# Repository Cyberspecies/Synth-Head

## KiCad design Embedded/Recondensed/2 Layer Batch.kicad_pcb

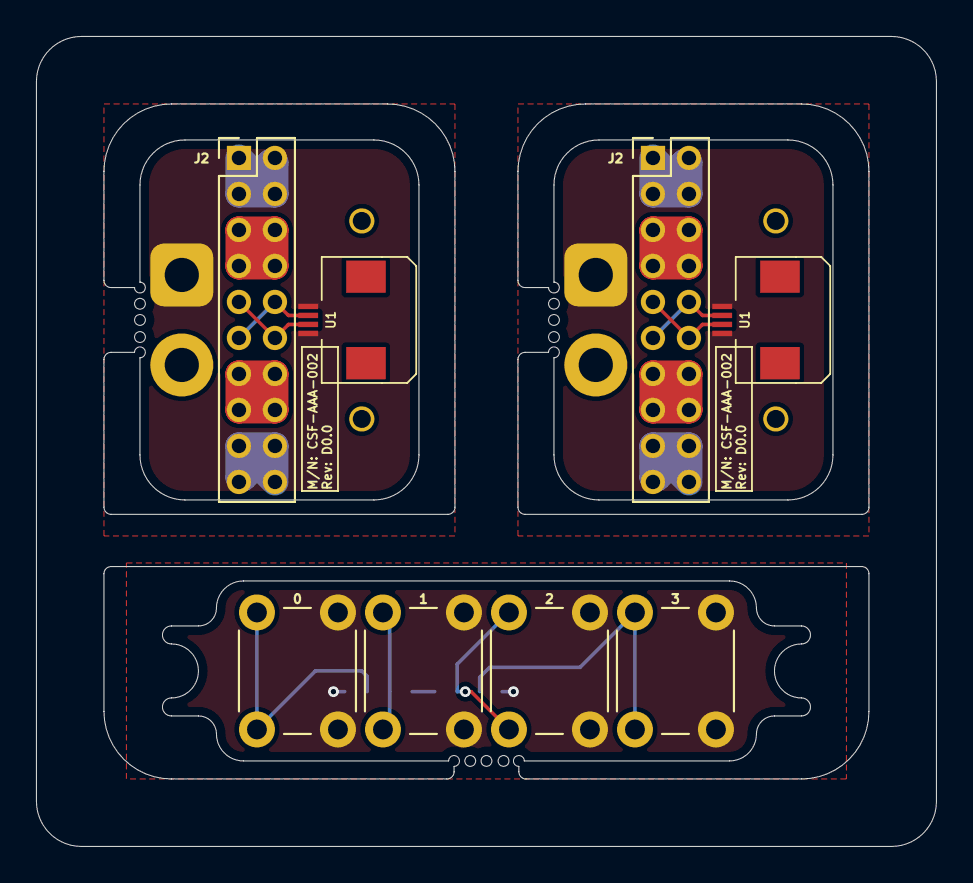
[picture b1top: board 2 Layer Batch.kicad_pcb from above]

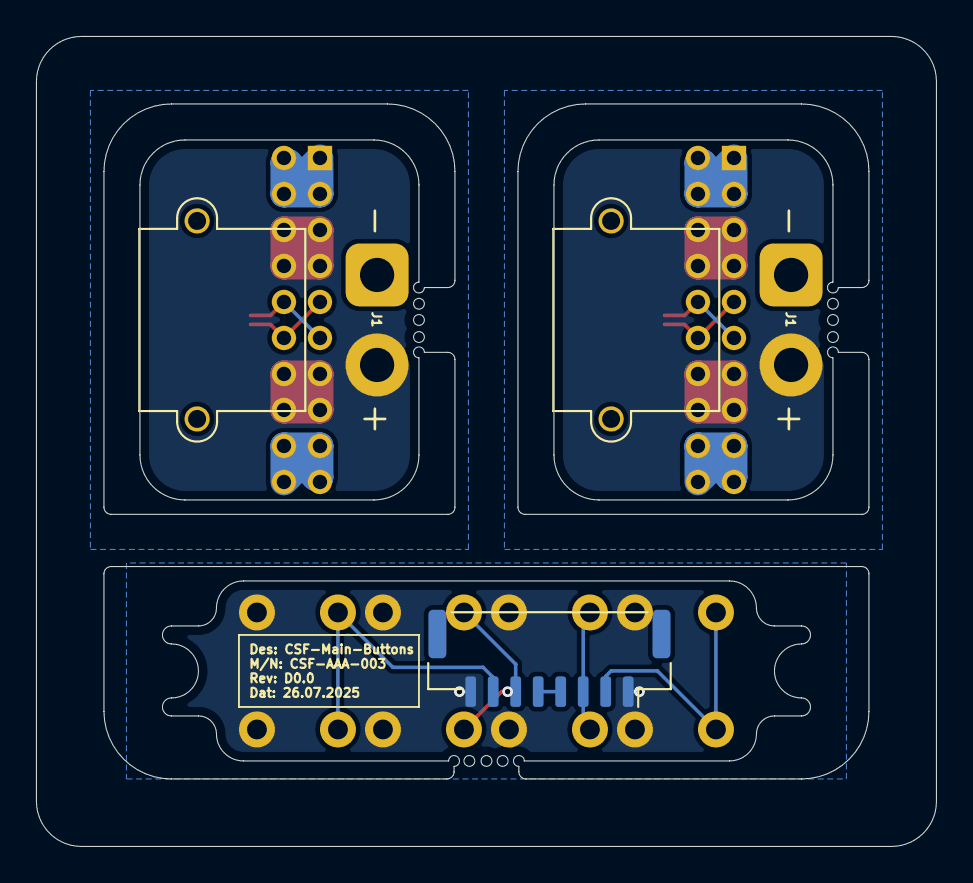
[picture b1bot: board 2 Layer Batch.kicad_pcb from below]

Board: 2 copper layers, 50.0 x 45.0 mm, 11 parts (3 on the bottom side), 9 nets.

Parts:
J1, J1#2: Substructure Power; AMASS_XT30PW-M_1x02_P2.50mm_Horizontal
J2, J2#2: Pogo Pins; PinHeader_2x10_P2.00mm_Vertical
J8: Buttons; JST_GH_SM08B-GHS-TB_1x08-1MP_P1.25mm_Horizontal
SW1: 0; SW_PUSH_6mm_H5mm
SW2: 1; SW_PUSH_6mm_H5mm
SW3: 2; SW_PUSH_6mm_H5mm
SW4: 3; SW_PUSH_6mm_H5mm
U1, U1#2: Substructure; FFC-4-0.5

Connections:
+3V3: J8.4, J8.5
+RAWVS: J1.2, J1#2.2, J2.5, J2.6, J2.7, J2.8, J2.13, J2.14, J2.15, J2.16, J2#2.5, J2#2.6, J2#2.7, J2#2.8, J2#2.13, J2#2.14, J2#2.15, J2#2.16
Button 0: J8.2, SW1.1
Button 1: J8.3, SW2.1
Button 2: J8.6, SW3.1
Button 3: J8.7, SW4.1
GND: J1.1, J1#2.1, J2.1, J2.2, J2.3, J2.4, J2.17, J2.18, J2.19, J2.20, J2#2.1, J2#2.2, J2#2.3, J2#2.4, J2#2.17, J2#2.18, J2#2.19, J2#2.20, J8.1, J8.8, SW1.2, SW2.2, SW3.2, SW4.2, U1.1, U1.4, U1#2.1, U1#2.4
Power UART RX: J2.9, J2.12, J2#2.9, J2#2.12, U1.2, U1#2.2
Power UART TX: J2.10, J2.11, J2#2.10, J2#2.11, U1.3, U1#2.3

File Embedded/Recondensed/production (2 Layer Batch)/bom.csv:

Designator,Footprint,Quantity,Value,LCSC Part #
"J1_2, J1",AMASS_XT30PW-M_1x02_P2.50mm_Horizontal,2,Substructure Power,
"J2_2, J2",PinHeader_2x10_P2.00mm_Vertical,2,Pogo Pins,
J8,JST_GH_SM08B-GHS-TB_1x08-1MP_P1.25mm_Horizontal,1,Buttons,
SW1,SW_PUSH_6mm_H5mm,1,0,
SW2,SW_PUSH_6mm_H5mm,1,1,
SW3,SW_PUSH_6mm_H5mm,1,2,
SW4,SW_PUSH_6mm_H5mm,1,3,
"U1_2, U1",FFC-4-0.5,2,Substructure,

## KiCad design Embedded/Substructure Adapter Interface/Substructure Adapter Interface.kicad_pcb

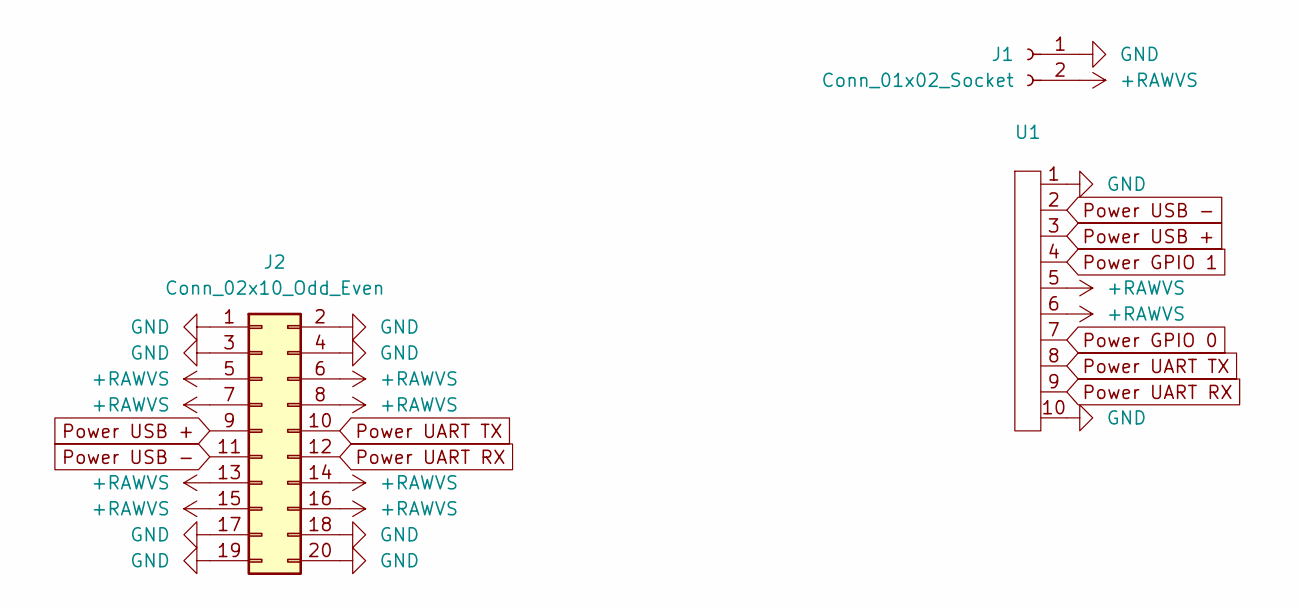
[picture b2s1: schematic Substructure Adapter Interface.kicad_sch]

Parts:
J1: Conn_01x02_Socket; AMASS_XT30PW-M_1x02_P2.50mm_Horizontal
J2: Conn_02x10_Odd_Even; PinHeader_2x10_P1.00mm_Vertical
U1: FFC 0.8mm 10P

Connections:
+RAWVS: J1.2, J2.5, J2.6, J2.7, J2.8, J2.13, J2.14, J2.15, J2.16, U1.5, U1.6
GND: J1.1, J2.1, J2.2, J2.3, J2.4, J2.17, J2.18, J2.19, J2.20, U1.1, U1.10
Power GPIO 0: U1.7
Power GPIO 1: U1.4
Power UART RX: J2.12, U1.9
Power UART TX: J2.10, U1.8
Power USB +: J2.9, U1.3
Power USB -: J2.11, U1.2

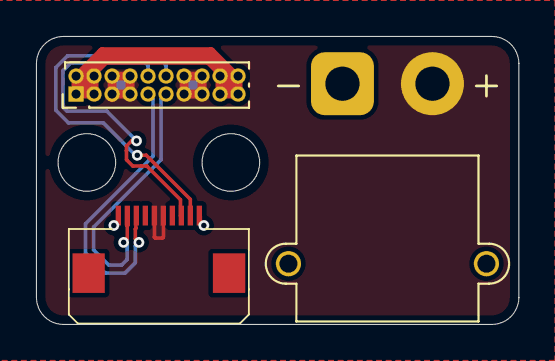
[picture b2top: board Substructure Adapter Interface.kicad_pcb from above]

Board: 2 copper layers, 26.8 x 16.0 mm, 3 parts (0 on the bottom side), 6 nets.

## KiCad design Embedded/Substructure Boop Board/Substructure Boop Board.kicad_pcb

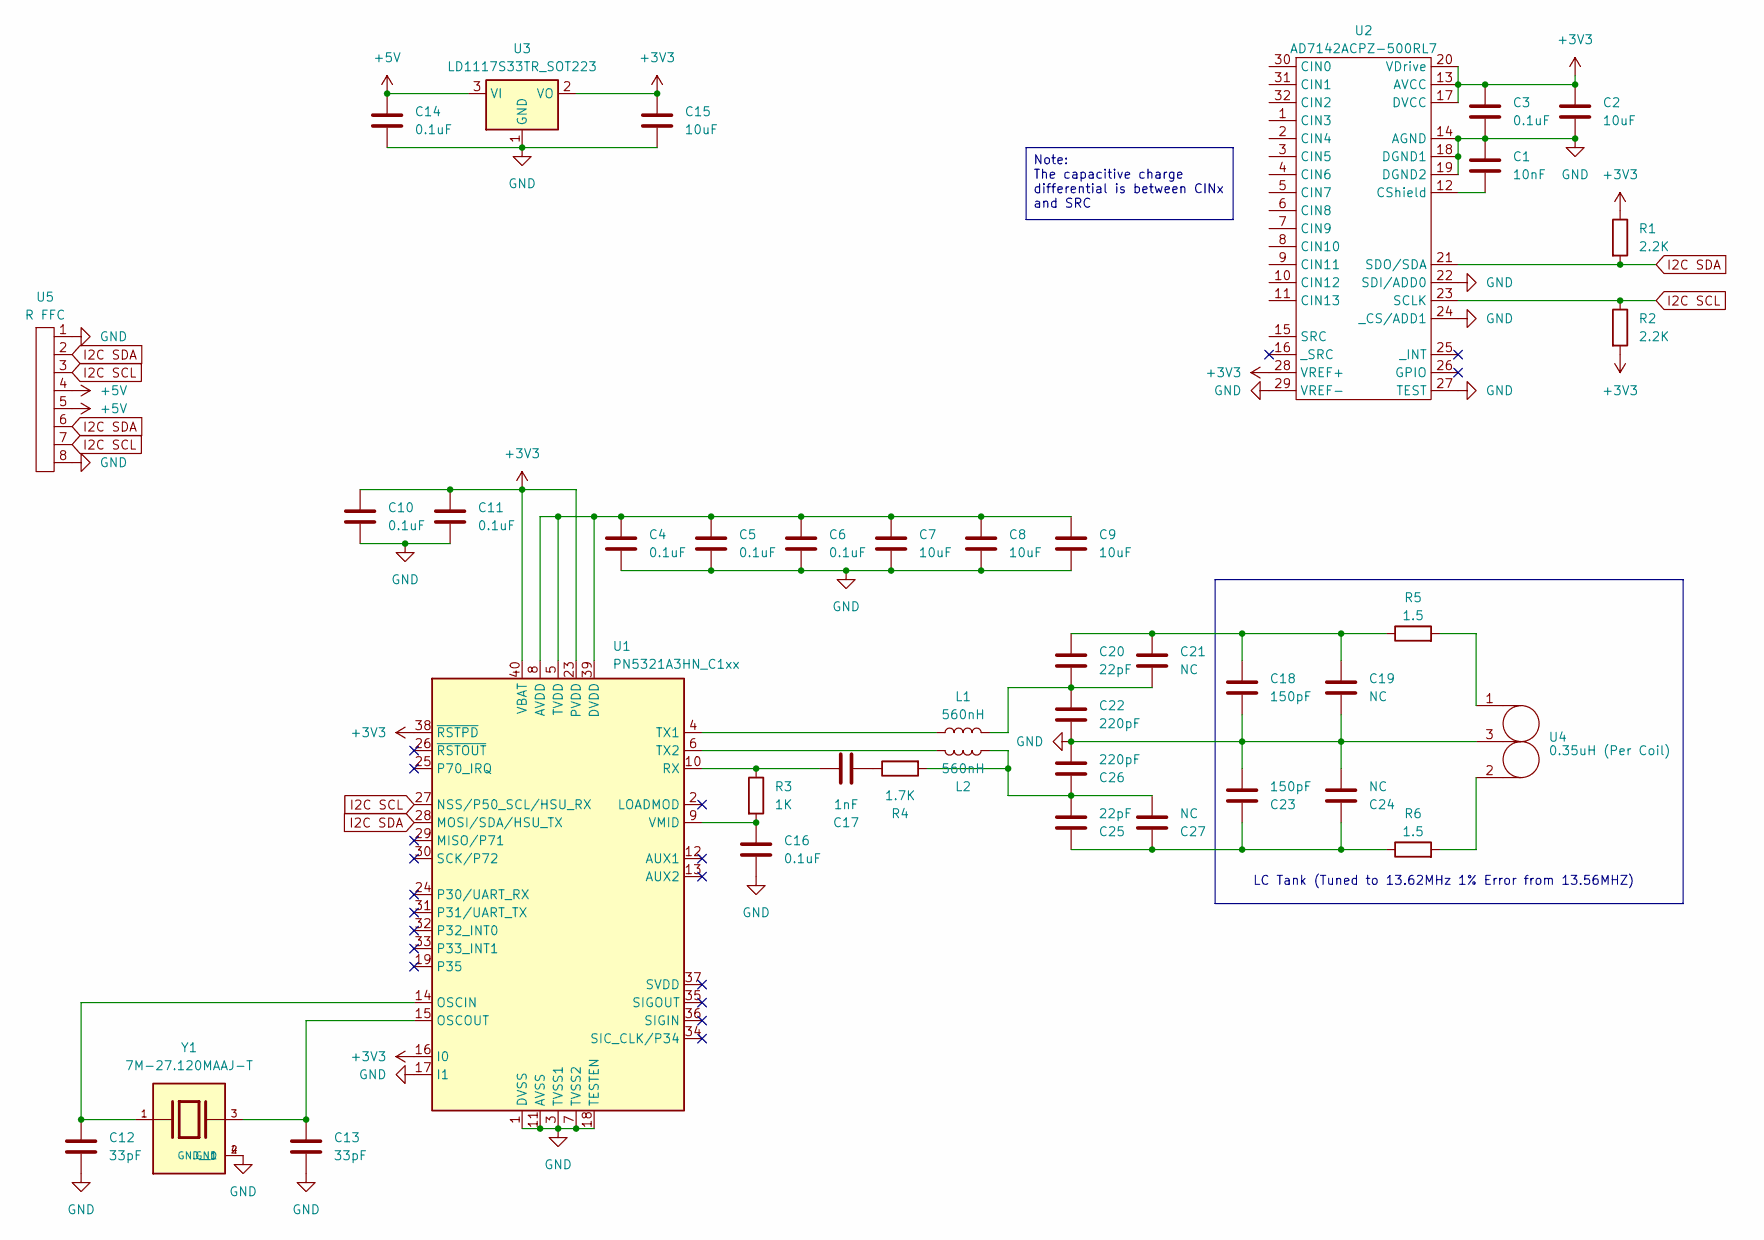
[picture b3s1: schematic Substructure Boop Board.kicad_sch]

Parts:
C1: 10nF; C_0402_1005Metric_Pad0.74x0.62mm_HandSolder
C2, C7, C8, C9: 10uF; C_0402_1005Metric_Pad0.74x0.62mm_HandSolder
C3, C4, C5, C6, C10, C11, C16: 0.1uF; C_0402_1005Metric_Pad0.74x0.62mm_HandSolder
C12, C13: 33pF; C_0402_1005Metric_Pad0.74x0.62mm_HandSolder
C14: 0.1uF; C_0603_1608Metric_Pad1.08x0.95mm_HandSolder
C15: 10uF; C_0603_1608Metric_Pad1.08x0.95mm_HandSolder
C17: 1nF; C_0402_1005Metric_Pad0.74x0.62mm_HandSolder
C18, C23: 150pF; C_0402_1005Metric_Pad0.74x0.62mm_HandSolder
C19, C21, C24, C27: NC; C_0402_1005Metric_Pad0.74x0.62mm_HandSolder
C20, C25: 22pF; C_0402_1005Metric_Pad0.74x0.62mm_HandSolder
C22, C26: 220pF; C_0402_1005Metric_Pad0.74x0.62mm_HandSolder
L1, L2: 560nH; L_0603_1608Metric_Pad1.05x0.95mm_HandSolder
R1, R2: 2.2K; C_0402_1005Metric_Pad0.74x0.62mm_HandSolder
R3: 1K; C_0402_1005Metric_Pad0.74x0.62mm_HandSolder
R4: 1.7K; C_0402_1005Metric_Pad0.74x0.62mm_HandSolder
R5, R6: 1.5; C_0402_1005Metric_Pad0.74x0.62mm_HandSolder
U1: PN5321A3HN_C1xx; HVQFN-40-1EP_6x6mm_P0.5mm_EP4.1x4.1mm; LCSC C28925
U2: AD7142ACPZ-500RL7; LFCSP-32-1EP_5x5mm_P0.5mm_EP3.1x3.1mm_ThermalVias; LCSC C208139
U3: LD1117S33TR_SOT223; SOT-223-3_TabPin2; LCSC C86781
U4: 0.35uH (Per Coil); 30 x 40 - 2 Pair 2 Layer 2 Turn Loop Antenna
U5: R FFC; FFC 0.8mm 8P
Y1: 7M-27.120MAAJ-T; XTAL_7M-27.120MAAJ-T; PARTREV N/A; DIGIKEY 887-1424-1-ND

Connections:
+3V3: C2.1, C3.1, C10.1, C11.1, C15.1, R1.1, R2.2, U1.16 (I0), U1.23 (PVDD), U1.38 (~RSTPD), U1.40 (VBAT), U2.13 (AVCC), U2.17 (DVCC), U2.20 (VDrive), U2.28 (VREF+), U3.2 (VO)
+5V: C14.1, U3.3 (VI), U5.4, U5.5
GND: C1.1, C2.2, C3.2, C4.2, C5.2, C6.2, C7.2, C8.2, C9.2, C10.2, C11.2, C12.2, C13.2, C14.2, C15.2, C16.2, C18.2, C19.2, C22.2, C23.2, C24.2, C26.1, U1.1 (DVSS), U1.3 (TVSS1), U1.7 (TVSS2), U1.11 (AVSS), U1.17 (I1), U1.18 (TESTEN), U1.41 (AVSS), U2.14 (AGND), U2.18 (DGND1), U2.19 (DGND2), U2.22 (SDI/ADD0), U2.24 (_CS/ADD1), U2.27 (TEST), U2.29 (VREF-), U3.1 (GND), U4.3, U5.1, U5.8, Y1.2 (GND), Y1.4 (GND__1)
I2C SCL: R2.1, U1.27 (NSS/P50_SCL/HSU_RX), U2.23 (SCLK), U5.3, U5.7
I2C SDA: R1.2, U1.28 (MOSI/SDA/HSU_TX), U2.21 (SDO/SDA), U5.2, U5.6
unnamed: C17.2, R4.1
unnamed: C18.1, C19.1, C20.1, C21.1, R5.1
unnamed: C20.2, C21.2, C22.1, L1.2
unnamed: C23.1, C24.1, C25.1, C27.1, R6.1
unnamed: C25.2, C26.2, C27.2, L2.2, R4.2
unnamed: R5.2, U4.1
unnamed: R6.2, U4.2
unnamed: C4.1, C5.1, C6.1, C7.1, C8.1, C9.1, U1.5 (TVDD), U1.8 (AVDD), U1.39 (DVDD)
unnamed: C12.1, U1.14 (OSCIN), Y1.1
unnamed: C13.1, U1.15 (OSCOUT), Y1.3
unnamed: C17.1, R3.1, U1.10 (RX)
unnamed: L1.1, U1.4 (TX1)
unnamed: L2.1, U1.6 (TX2)
unnamed: C16.1, R3.2, U1.9 (VMID)
unnamed: C1.2, U2.12 (CShield)

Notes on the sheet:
LC Tank (Tuned to 13.62MHz 1% Error from 13.56MHZ)
Note: The capacitive charge differential is between CINx and SRC

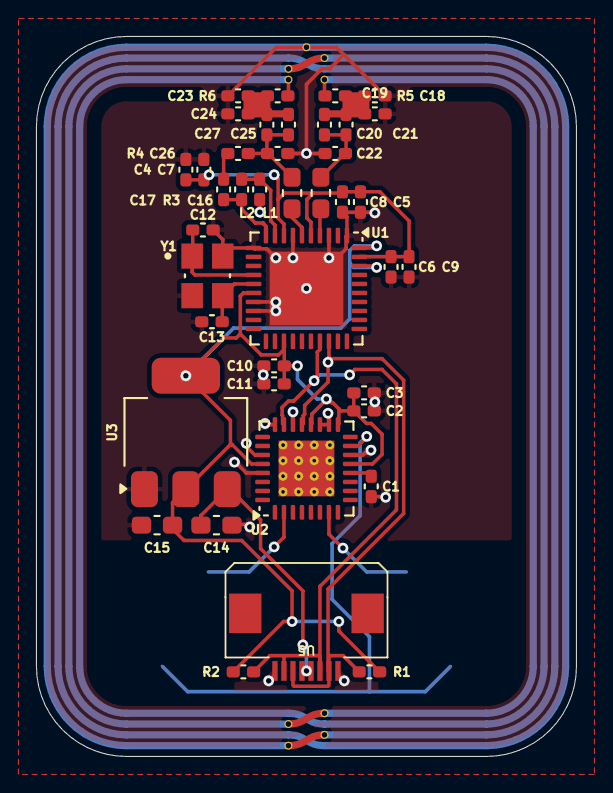
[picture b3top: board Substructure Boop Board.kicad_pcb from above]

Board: 2 copper layers, 30.0 x 40.0 mm, 41 parts (1 on the bottom side), 20 nets.

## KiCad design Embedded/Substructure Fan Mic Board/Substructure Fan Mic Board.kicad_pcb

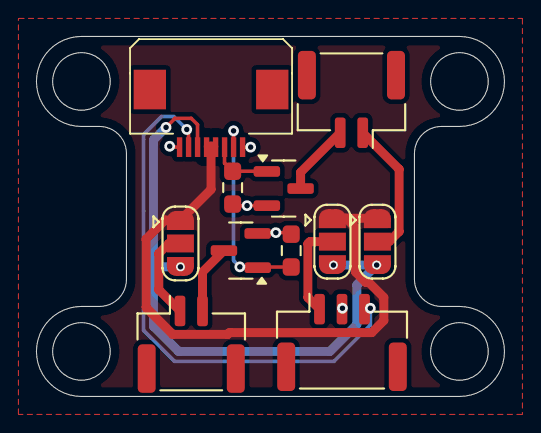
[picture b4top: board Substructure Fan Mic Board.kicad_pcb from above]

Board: 2 copper layers, 26.0 x 20.0 mm, 11 parts (0 on the bottom side), 11 nets.

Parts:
J1: Conn_01x03_Socket; JST_GH_SM03B-GHS-TB_1x03-1MP_P1.25mm_Horizontal
J2, J3: Conn_01x02_Socket; JST_GH_SM02B-GHS-TB_1x02-1MP_P1.25mm_Horizontal
JP1, JP2, JP3: SolderJumper_3_Open; SolderJumper-3_P1.3mm_Open_RoundedPad1.0x1.5mm
Q1, Q2: DMG3402L; SOT-23
R1, R2: 10K; R_0603_1608Metric_Pad0.98x0.95mm_HandSolder
U2: F FFC; FFC 0.8mm 8P

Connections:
+3V3: JP1.3 (B), JP2.3 (B), JP3.3 (B), U2.6
+5V: JP1.1 (A), JP2.1 (A), JP3.1 (A), U2.4, U2.5
Fan 0: Q1.1 (G), R1.1, U2.3
Fan 1: Q2.1 (G), R2.1, U2.2
GND: J1.2, Q1.2 (S), Q2.2 (S), R1.2, R2.2, U2.1, U2.8
Mic Analog: J1.3, U2.7
unnamed: J1.1, JP1.2 (C)
unnamed: J2.1, JP2.2 (C)
unnamed: J2.2, Q1.3 (D)
unnamed: J3.1, JP3.2 (C)
unnamed: J3.2, Q2.3 (D)

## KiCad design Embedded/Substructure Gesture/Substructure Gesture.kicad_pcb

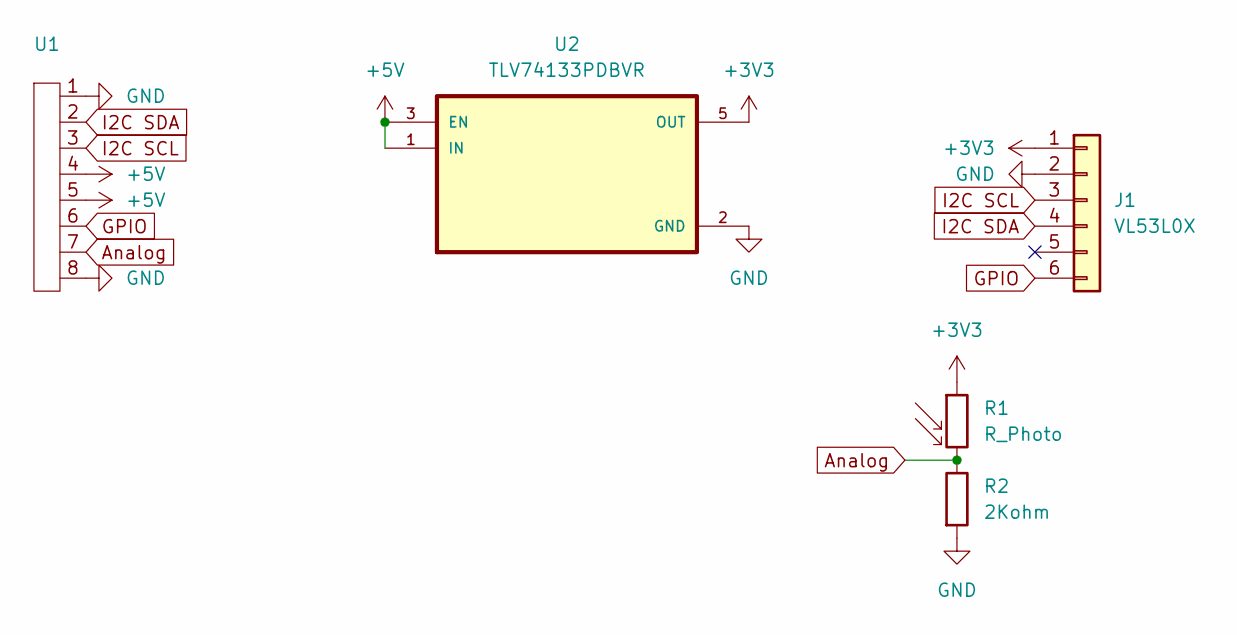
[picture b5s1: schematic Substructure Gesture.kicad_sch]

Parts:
J1: VL53L0X; PinHeader_1x06_P2.54mm_Vertical
R1: R_Photo; R_LDR_5.1x4.3mm_P3.4mm_Vertical
R2: 2Kohm; R_0603_1608Metric_Pad0.98x0.95mm_HandSolder
U1: FFC 0.8mm 8P
U2: TLV74133PDBVR; SOT95P280X145-5N

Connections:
+3V3: J1.1, R1.1, U2.5 (OUT)
+5V: U1.4, U1.5, U2.1 (IN), U2.3 (EN)
Analog: R1.2, R2.1, U1.7
GND: J1.2, R2.2, U1.1, U1.8, U2.2 (GND)
GPIO: J1.6, U1.6
I2C SCL: J1.3, U1.3
I2C SDA: J1.4, U1.2

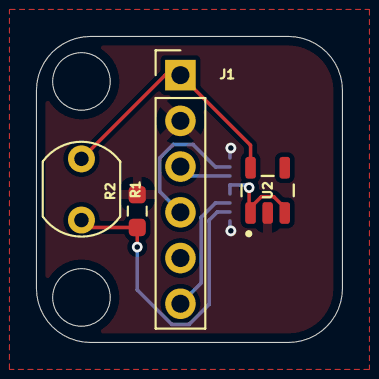
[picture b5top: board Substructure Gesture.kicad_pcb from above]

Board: 2 copper layers, 17.0 x 17.0 mm, 5 parts (1 on the bottom side), 7 nets.

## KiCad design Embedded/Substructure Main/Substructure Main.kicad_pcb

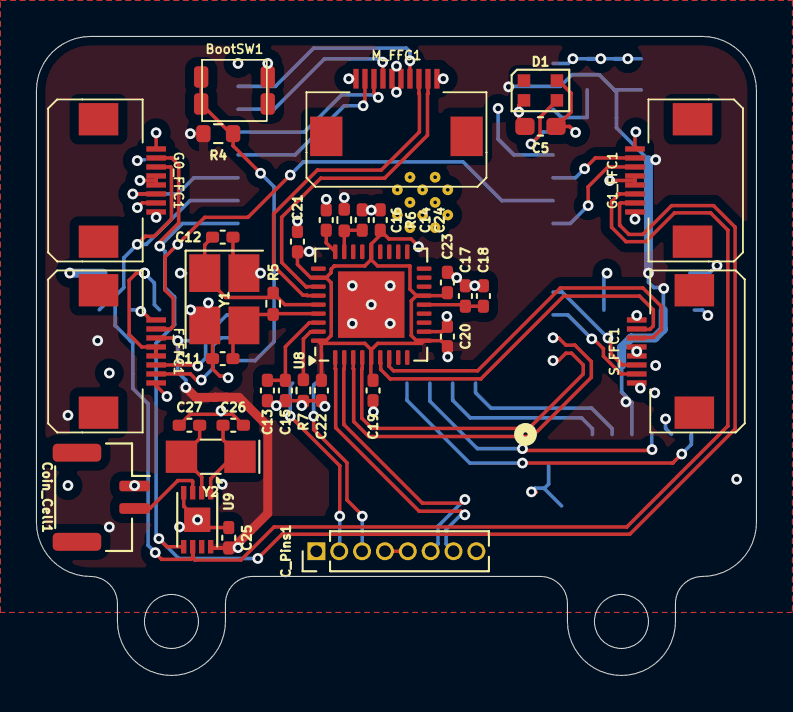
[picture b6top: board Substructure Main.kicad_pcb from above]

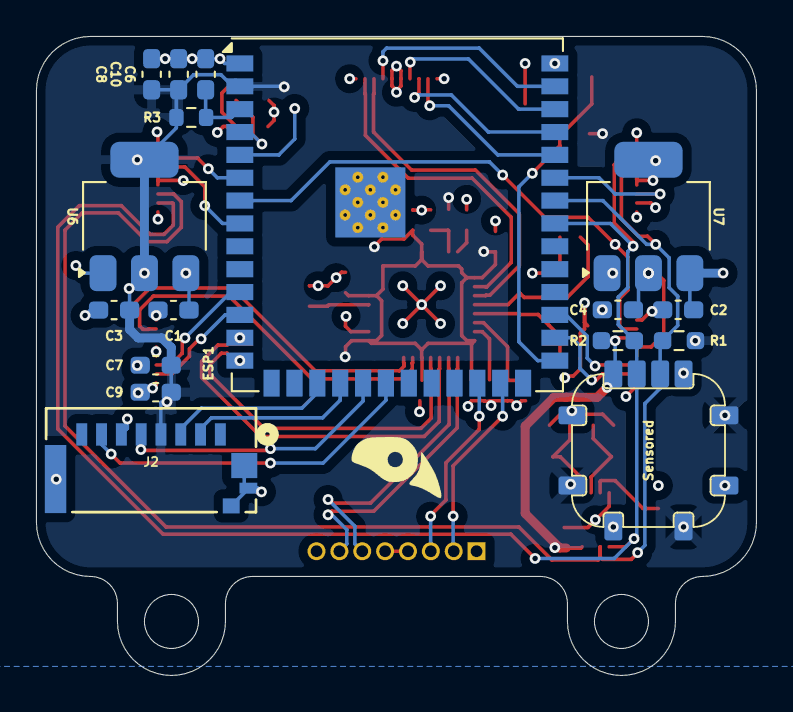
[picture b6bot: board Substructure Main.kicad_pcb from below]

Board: 4 copper layers, 40.0 x 35.5 mm, 52 parts (17 on the bottom side), 46 nets.

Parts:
BootSW1: SW_Push; R-667843
C1, C2: 0.1uf; C_0603_1608Metric_Pad1.08x0.95mm_HandSolder
C3, C4: 10uf; C_0603_1608Metric_Pad1.08x0.95mm_HandSolder
C5, C6: 1uF; C_0603_1608Metric_Pad1.08x0.95mm_HandSolder
C7, C8: 22uF; C_0603_1608Metric_Pad1.08x0.95mm_HandSolder
C9, C10: 0.1uF; C_0603_1608Metric_Pad1.08x0.95mm_HandSolder
C11, C12: 18pf; C_0402_1005Metric_Pad0.74x0.62mm_HandSolder
C13, C17: 1uF; C_0402_1005Metric_Pad0.74x0.62mm_HandSolder
C14, C15, C16, C18, C19, C20, C21, C22, C23, C24, C25: 0.1uF; C_0402_1005Metric_Pad0.74x0.62mm_HandSolder
C26: 10pf; C_0402_1005Metric_Pad0.74x0.62mm_HandSolder
C27: 12pf; C_0402_1005Metric_Pad0.74x0.62mm_HandSolder
C_Pins1: C Pins; PinHeader_1x08_P1.27mm_Vertical
Coin_Cell1: Coin Cell; JST_GH_SM02B-GHS-TB_1x02-1MP_P1.25mm_Horizontal
D1: WS2812B-2020; LED_WS2812B-2020_PLCC4_2.0x2.0mm
ESP1: ESP32-S3-WROOM-1U
F_FFC1: F FFC; FFC-8-0.5
G0_FFC1: G0 FFC; FFC-8-0.5
G1_FFC1: G1 FFC; FFC-8-0.5
J2: MicroSD; MicroSD_473092651
M_FFC1: M FFC; FFC-10-0.5
R1, R2: 10K; R_0603_1608Metric_Pad0.98x0.95mm_HandSolder
R3, R4: 10K; R_0603_1608Metric
R5: 1M; R_0402_1005Metric_Pad0.72x0.64mm_HandSolder
R6: 100K; R_0402_1005Metric_Pad0.72x0.64mm_HandSolder
R7: 12K; R_0402_1005Metric_Pad0.72x0.64mm_HandSolder
S_FFC1: S FFC; FFC-8-0.5
U6: LD1117S33TR_SOT223; SOT-223-3_TabPin2
U7: LD1117S50TR_SOT223; SOT-223-3_TabPin2
U8: USB2513B_Bi; QFN-36-1EP_6x6mm_P0.5mm_EP3.7x3.7mm
U9: MCP7940N-xMNY; DFN-8-1EP_3x2mm_P0.5mm_EP1.36x1.46mm
U11: Sensored
Y1: TSX-3225 24MF18X-C0; Crystal_SMD_SeikoEpson_TSX3225-4Pin_3.2x2.5mm_HandSoldering
Y2: CM7V-T1A; Crystal_SMD_MicroCrystal_CC7V-T1A-2Pin_3.2x1.5mm_HandSolder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

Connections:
+3V3: C3.1, C7.1, C8.1, C9.1, C10.1, C19.1, C20.1, C21.1, C22.1, C23.1, C24.1, C25.1, ESP1.2 (3V3), F_FFC1.3, J2.4, R1.1, R2.1, R3.1, R4.1, R6.2, U6.2 (VO), U8.5 (VDDA33), U8.10 (VDDA33), U8.15 (VDD33), U8.23 (VDD33), U8.29 (VDDA33), U8.36 (VDDA33), U9.8 (VCC), U11.3V3
+5V: C4.1, C5.1, C_Pins1.4, C_Pins1.5, D1.4 (VDD), F_FFC1.4, F_FFC1.5, G0_FFC1.4, G0_FFC1.5, G1_FFC1.4, G1_FFC1.5, S_FFC1.4, S_FFC1.5, U7.2 (VO)
+5VP: C16.1, U8.27 (VBUS_DET)
+5VS: C1.1, C2.1, M_FFC1.5, M_FFC1.6, U6.3 (VI), U7.3 (VI)
Debug LED: D1.3 (DIN), ESP1.4 (GPIO4/TOUCH4/ADC1_CH3)
Fan 0: ESP1.29 (SPIIO7/GPIO36/FSPICLK/SUBSPICLK), F_FFC1.6
Fan 1: ESP1.28 (SPIIO6/GPIO35/FSPID/SUBSPID), F_FFC1.7
GND: BootSW1.2, C1.2, C2.2, C3.2, C4.2, C5.2, C6.1, C7.2, C8.2, C9.2, C10.2, C11.1, C12.1, C13.2, C14.2, C15.2, C16.2, C17.2, C18.2, C19.2, C20.2, C21.2, C22.2, C23.2, C24.2, C25.2, C26.2, C27.2, C_Pins1.1, C_Pins1.8, Coin_Cell1.1, D1.2 (VSS), ESP1.1 (GND), ESP1.40 (GND), ESP1.41 (GND), F_FFC1.1, F_FFC1.8, G0_FFC1.1, G0_FFC1.8, G1_FFC1.1, G1_FFC1.8, J2.6, J2.G1, J2.G2, J2.G3, J2.G4, M_FFC1.1, M_FFC1.10, R7.1, S_FFC1.1, S_FFC1.8, U6.1 (GND), U7.1 (GND), U8.11 (TEST), U8.37 (VSS), U9.4 (VSS), U9.9 (EP), U11.GND, Y1.2, Y1.4
Gesture GPIO 1: ESP1.35 (MTMS/GPIO42), G0_FFC1.6
Gesture GPIO 2: ESP1.8 (GPIO15/U0RTS/ADC2_CH4/XTAL_32K_P), G1_FFC1.6
HUD UART RX: C_Pins1.2, ESP1.25 (GPIO48/SPICLK_N/SUBSPICLK_N_DIFF)
HUD UART TX: C_Pins1.3, ESP1.24 (GPIO47/SPICLK_P/SUBSPICLK_P_DIFF)
HUD USB +: C_Pins1.6, U8.2 (USBDP_DN1/PRT_DIS_P1)
HUD USB -: C_Pins1.7, U8.1 (USBDM_DN1/PRT_DIS_M1)
I2C SCL: ESP1.34 (MTDI/GPIO41/CLK_OUT1), G0_FFC1.3, G1_FFC1.3, R1.2, U9.6 (SCL), U11.SCL
I2C SDA: ESP1.33 (MTDO/GPIO40/CLK_OUT2), G0_FFC1.2, G1_FFC1.2, R2.2, U9.5 (SDA), U11.SDA
Main USB +: ESP1.14 (GPIO20/U1CTS/ADC2_CH9/CLK_OUT1/USB_D+), U8.4 (USBDP_DN2/PRT_DIS_P2)
Main USB -: ESP1.13 (GPIO19/U1RTS/ADC2_CH8/CLK_OUT2/USB_D-), U8.3 (USBDM_DN2/PRT_DIS_M2)
Mic Analog: ESP1.7 (GPIO7/TOUCH7/ADC1_CH6), F_FFC1.2
unnamed: Coin_Cell1.2, U9.3 (VBAT)
unnamed: C6.2, ESP1.3 (EN), R3.2
unnamed: BootSW1.1, ESP1.27 (GPIO0/BOOT), R4.2
unnamed: C17.1, C18.1, U8.14 (CRFILT)
unnamed: C13.1, C15.1, U8.34 (PLLFILT)
unnamed: R7.2, U8.35 (RBIAS)
unnamed: C14.1, R6.1, U8.26 (RESET_N)
unnamed: C11.2, R5.2, U8.33 (XTALIN/CLKIN), Y1.3
unnamed: C12.2, R5.1, U8.32 (XTALOUT), Y1.1
unnamed: C26.1, U9.1 (X1), Y2.1
unnamed: C27.1, U9.2 (X2), Y2.2
Photoresistor 1: ESP1.5 (GPIO5/TOUCH5/ADC1_CH4), G0_FFC1.7
Photoresistor 2: ESP1.6 (GPIO6/TOUCH6/ADC1_CH5), G1_FFC1.7
Power GPIO 0: ESP1.38 (GPIO2/TOUCH2/ADC1_CH1), M_FFC1.4
Power GPIO 1: ESP1.39 (GPIO1/TOUCH1/ADC1_CH0), M_FFC1.7
Power UART RX: ESP1.36 (U0RXD/GPIO44/CLK_OUT2), M_FFC1.2
Power UART TX: ESP1.37 (U0TXD/GPIO43/CLK_OUT1), M_FFC1.3
Power USB +: M_FFC1.8, U8.31 (USBDP_UP)
Power USB -: M_FFC1.9, U8.30 (USBDM_UP)
SD SPI CLK: ESP1.19 (GPIO11/TOUCH11/ADC2_CH0/FSPID/FSPIIO5/S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), J2.5
SD SPI CS: ESP1.18 (GPIO10/TOUCH10/ADC1_CH9/FSPICS0/FSPIIO4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), J2.2
SD SPI MISO: ESP1.20 (GPIO12/TOUCH12/ADC2_CH1/FSPICLK/FSPIIO6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), J2.7
SD SPI MOSI: ESP1.17 (GPIO9/TOUCH9/ADC1_CH8/FSPIHD/SUBSPIHD), J2.3
Snoot UART RX: ESP1.12 (GPIO8/TOUCH8/ADC1_CH7/SUBSPICS1), S_FFC1.2
Snoot UART TX: ESP1.11 (GPIO18/U1RXD/ADC2_CH7/CLK_OUT3), S_FFC1.3
Snoot USB +: S_FFC1.6, U8.7 (USBDP_DN3/PRT_DIS_P3)
Snoot USB -: S_FFC1.7, U8.6 (USBDM_DN3/PRT_DIS_M3)

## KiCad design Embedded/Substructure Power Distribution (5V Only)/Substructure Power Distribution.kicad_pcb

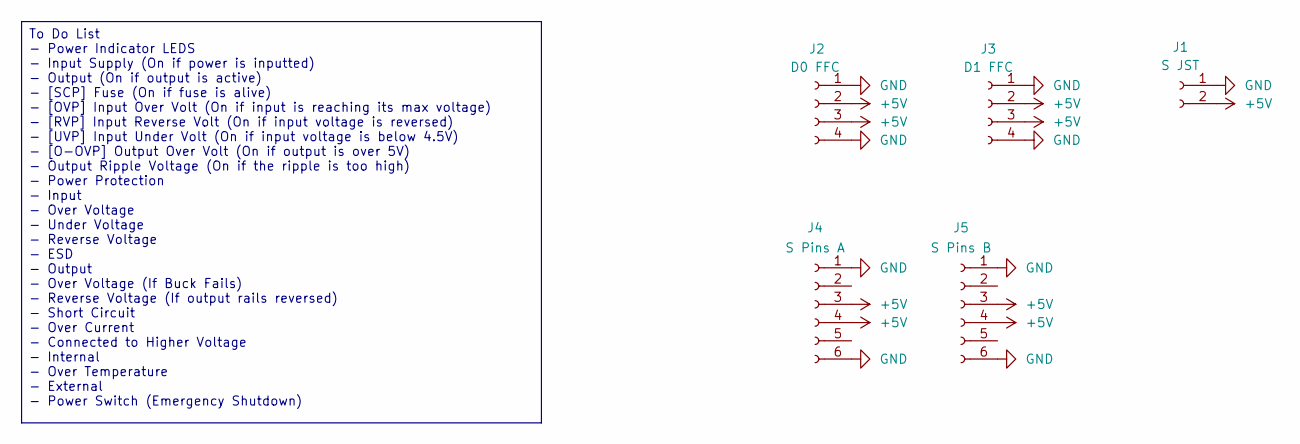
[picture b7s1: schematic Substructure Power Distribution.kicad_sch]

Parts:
J1: S JST; AMASS_XT30PW-M_1x02_P2.50mm_Horizontal
J2: D0 FFC; JST_XH_B4B-XH-A_1x04_P2.50mm_Vertical
J3: D1 FFC; JST_XH_B4B-XH-A_1x04_P2.50mm_Vertical
J4: S Pins A; PinHeader_1x06_P2.54mm_Vertical
J5: S Pins B; PinHeader_1x06_P2.54mm_Vertical

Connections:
+5V: J1.2, J2.2, J2.3, J3.2, J3.3, J4.3, J4.4, J5.3, J5.4
GND: J1.1, J2.1, J2.4, J3.1, J3.4, J4.1, J4.6, J5.1, J5.6

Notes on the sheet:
To Do List - Power Indicator LEDS - Input Supply (On if power is inputted) - Output (On if output is active) - [SCP] Fuse (On if fuse is alive) - [OVP] Input Over Volt (On if input is reaching its max voltage) - [RVP] Input Reverse Volt (On if input voltage is reversed) - [UVP] Input Under Volt (On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

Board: 2 copper layers, 5 parts (2 on the bottom side), 2 nets, no tracks yet.
